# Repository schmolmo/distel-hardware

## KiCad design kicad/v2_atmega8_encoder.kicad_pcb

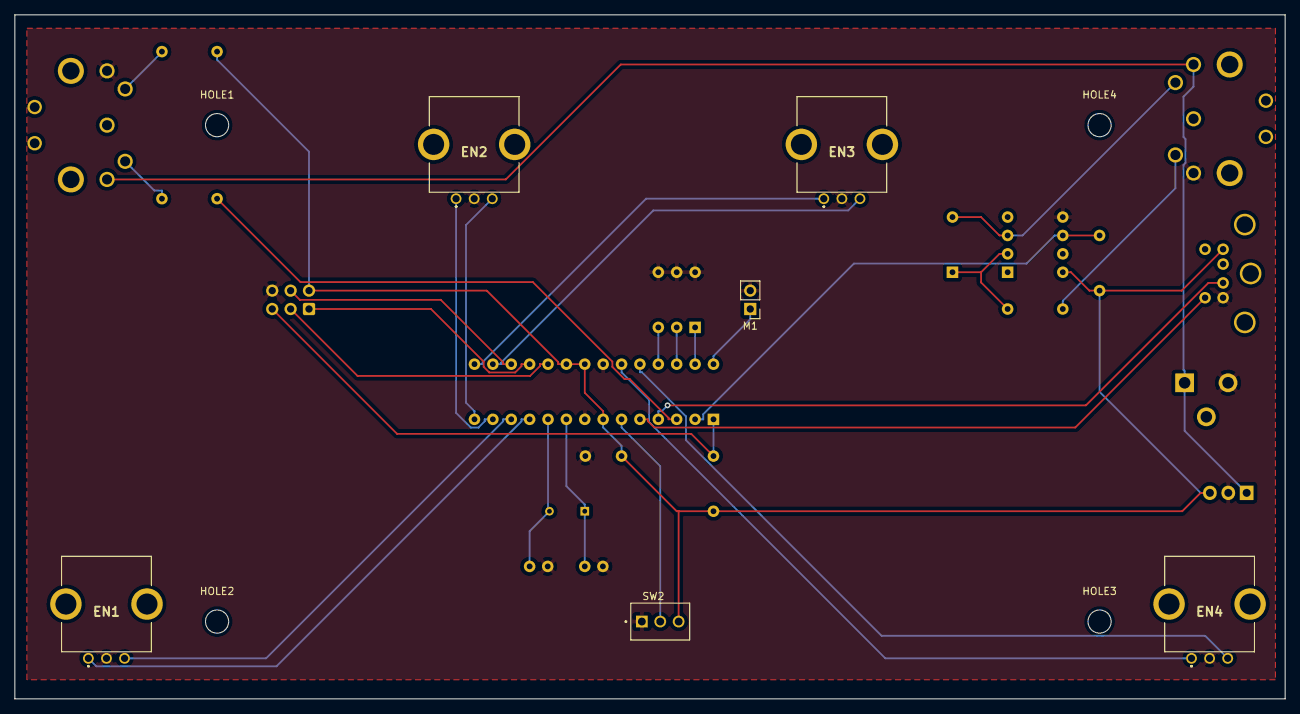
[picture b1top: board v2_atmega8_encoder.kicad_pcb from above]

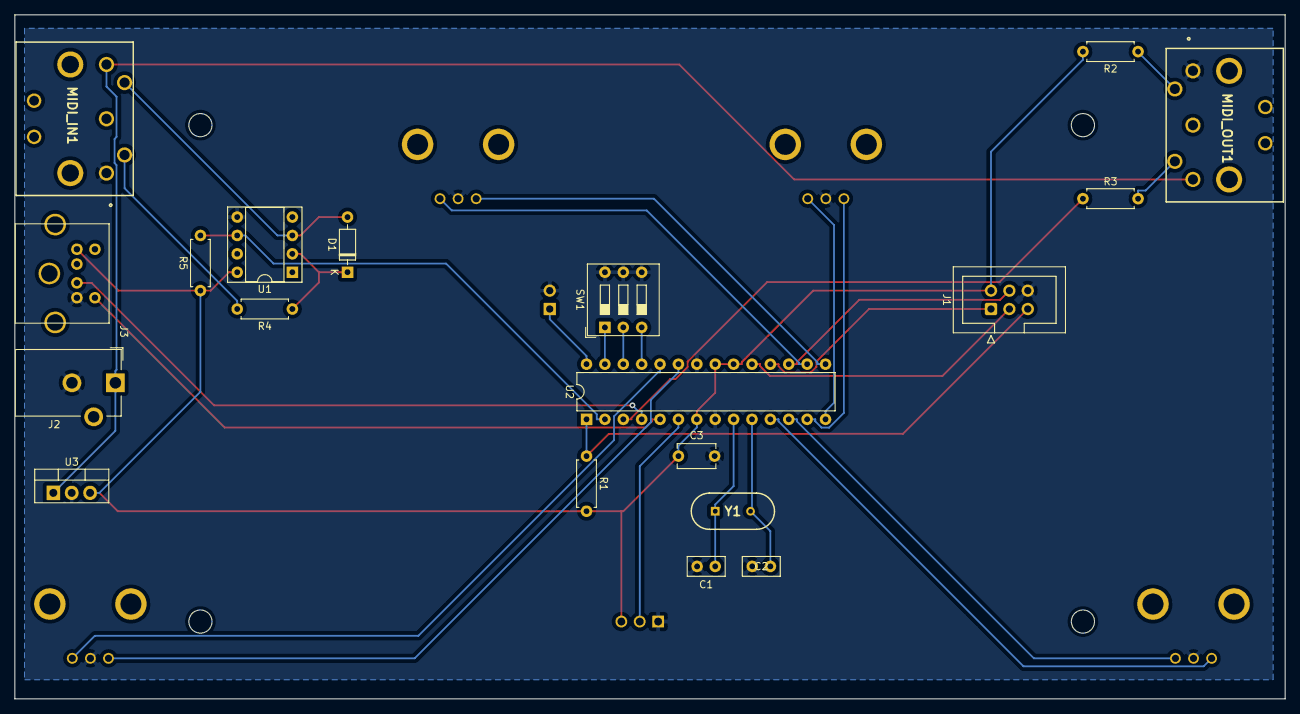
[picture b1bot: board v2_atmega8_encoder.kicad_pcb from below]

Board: 2 copper layers, 175.5 x 94.5 mm, 29 parts (19 on the bottom side), 31 nets.

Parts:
C1, C2: 22p; C_Disc_D5.0mm_W2.5mm_P2.50mm
C3: 100n; C_Disc_D5.1mm_W3.2mm_P5.00mm
D1: 1N914; D_DO-35_SOD27_P7.62mm_Horizontal
EN1, EN2, EN3, EN4: Rotary_Encoder; EC12E2430404
HOLE1, HOLE2, HOLE3, HOLE4: MountingHole_3.2mm_M3
J1: AVR-ISP-6; IDC-Header_2x03_P2.54mm_Vertical
J2: Jack-DC; BarrelJack_CUI_PJ-102AH_Horizontal
J3: Mini-DIN-6; mini-DIN 6
M1: Motor_DC; PinHeader_1x02_P2.54mm_Vertical
MIDI_IN1: DIN-5; MAB-5-SH
MIDI_OUT1: DIN-5; MAB-5-SH
R1: 10K; R_Axial_DIN0207_L6.3mm_D2.5mm_P7.62mm_Horizontal
R2, R3, R4, R5: 220; R_Axial_DIN0207_L6.3mm_D2.5mm_P7.62mm_Horizontal
SW1: SW_DIP_x03; SW_DIP_SPSTx03_Slide_9.78x9.8mm_W7.62mm_P2.54mm
SW2: SW_SPDT; SW_2MS1T1B1M2QES
U1: 6N138; DIP-8_W7.62mm_Socket
U2: ATmega8-16PU; DIP-28_W7.62mm
U3: L7805; TO-220-3_Vertical
Y1: 16 Mhz; ABL

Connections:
+5V: C3.1, J1.2, J3.3, R1.2, R2.2, R5.1, SW2.3, U1.8, U2.7, U2.20, U2.21, U3.3
+12V: J2.1, MIDI_IN1.3, MIDI_OUT1.3, U3.1
GND: C1.2, C2.2, C3.2, EN1.C, EN2.C, EN3.C, EN4.C, J1.6, J2.2, J3.4, M1.2, MIDI_IN1.1, MIDI_OUT1.1, SW1.4, SW1.5, SW1.6, SW2.1, U1.5, U2.8, U2.22, U3.2
unnamed: C1.1, U2.9, Y1.1
unnamed: C2.1, U2.10, Y1.2
unnamed: D1.1, R4.1, U1.2
unnamed: D1.2, MIDI_IN1.5, U1.3
unnamed: J1.1, U2.18
unnamed: J1.3, U2.19
unnamed: J1.4, U2.17
unnamed: J1.5, R1.1, U2.1
unnamed: J3.2, U2.4
unnamed: J3.6, U2.5
unnamed: M1.1, U2.28
unnamed: MIDI_IN1.4, R4.2
unnamed: MIDI_OUT1.4, R2.1
unnamed: MIDI_OUT1.5, R3.2
unnamed: SW1.1, U2.27
unnamed: SW1.2, U2.26
unnamed: SW1.3, U2.25
unnamed: SW2.2, U2.6
Pin11: EN1.A, U2.11
Pin12: EN1.B, U2.12
Pin13: EN2.A, U2.13
Pin14: EN2.B, U2.14
Pin15: EN3.A, U2.15
Pin16: EN3.B, U2.16
Pin23: EN4.A, U2.23
Pin24: EN4.B, U2.24
RX: R5.2, U1.6, U2.2
TX: R3.1, U2.3

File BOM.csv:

ID,Bezeichner,Stückzahl,Bezeichnung,Manufacturer Part No.,Mouser 
1,"HOLE4,HOLE3,HOLE1,HOLE2",4,MountingHole_3.2mm_M3,,
2,SW1,1,DIP SWITCH 3 PIN,,
3,M1,1,Miniature Vibration Motor,,
4,R1,1,10K,,
5,"C1,C2",2,22p,,
6,Y1,1,16 Mhz,,
7,U3,1,L7805,,
8,U1,1,6N138,,
9,SW2,1,SPDT Switch ,Dailywell 2MS1T1B1M2QES,118-2MS1T1B1M2QES 
10,"R5,R4,R3,R2",4,220 Ohm Resistor,,
11,"MIDI_OUT1,MIDI_IN1",2,DIN-5 Socket,Hirschmann MAB-5 SH,566-MAB5SH
12,J2,1,Jack-DC,CUI Devices PJ-102AH,490-PJ-102AH
13,J1,1,2x3 Pin Header,,
14,"EN4,EN3,EN2,EN1",4,"Rotary Encoder, 24 PPR",ALPS EC12E2430804,688-EC12E2430804
15,C3,1,100n,,
16,J3,1,Mini-DIN-6 Socket,TE Connectivity 5749266-1,571-5749266-1
17,U2,1,ATmega8-16PU,,
18,D1,1,1N914,,

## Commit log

2024-01-31 upload files
2024-01-31 add DIP-Sockets and Knobs
2024-01-31 edit ignore
2024-02-03 add lasercut files
2024-02-09 not working
2024-02-09 slightly better
2024-02-09 another small change
2024-02-11 slower transfer rate
